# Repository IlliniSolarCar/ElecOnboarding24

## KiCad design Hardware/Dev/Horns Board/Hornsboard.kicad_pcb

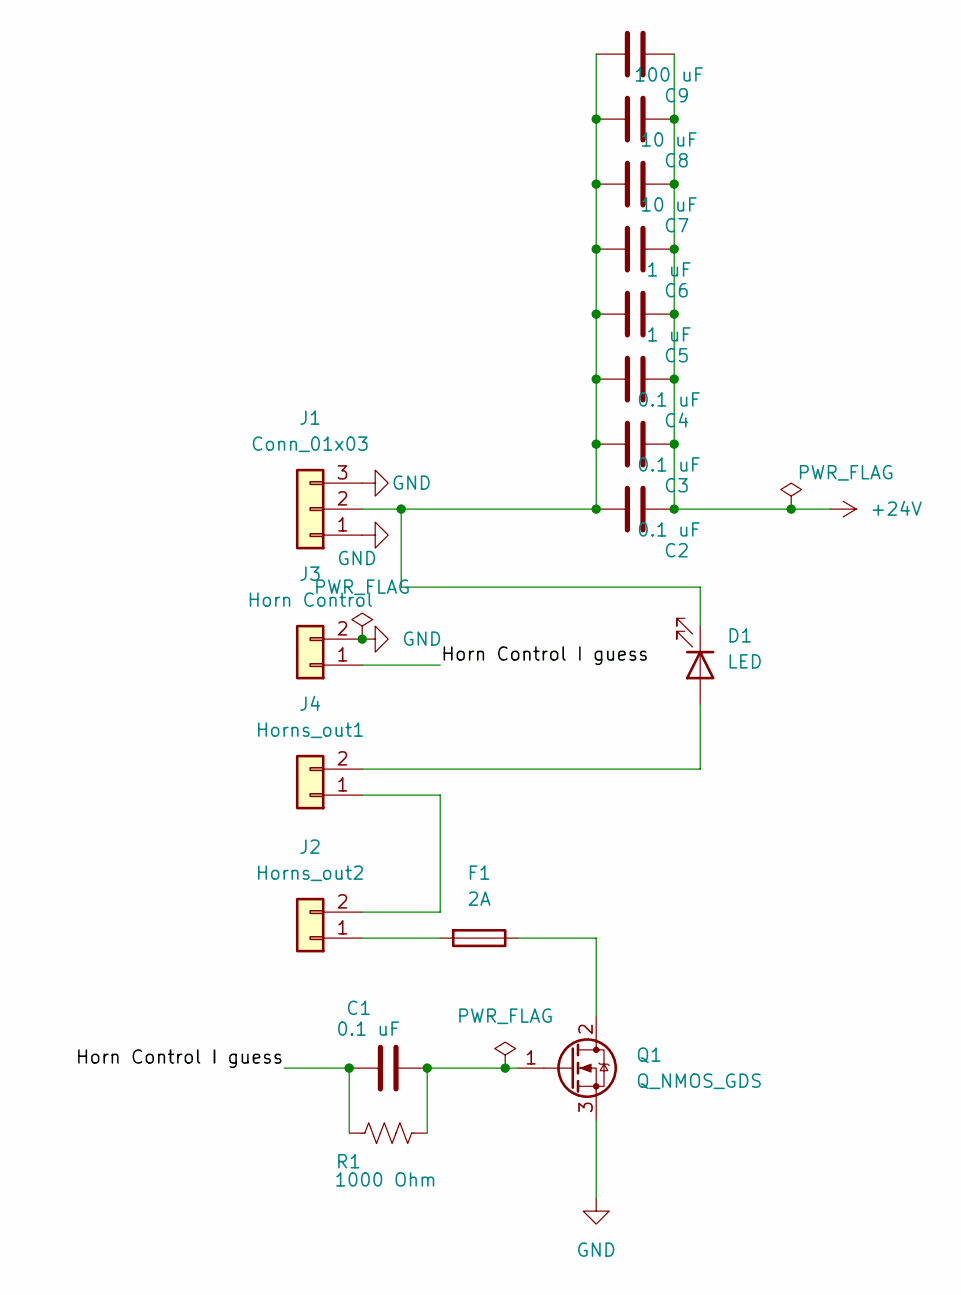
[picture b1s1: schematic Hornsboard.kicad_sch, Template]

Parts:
C1, C2, C3, C4: 0.1 uF; C_0603_1608Metric_Pad1.08x0.95mm_HandSolder
C5, C6: 1 uF; C_0603_1608Metric_Pad1.08x0.95mm_HandSolder
C7, C8: 10 uF; C_0603_1608Metric_Pad1.08x0.95mm_HandSolder
C9: 100 uF; C_0603_1608Metric_Pad1.08x0.95mm_HandSolder
D1: LED; LED_0603_1608Metric_Pad1.05x0.95mm_HandSolder
F1: 2A; Fuse_0603_1608Metric
J1: Conn_01x03; Molex_Micro-Fit_3.0_43650-0300_1x03_P3.00mm_Horizontal
J2: Horns_out2; Molex_Micro-Fit_3.0_43650-0200_1x02_P3.00mm_Horizontal
J3: Horn Control; Molex_Micro-Fit_3.0_43650-0200_1x02_P3.00mm_Horizontal
J4: Horns_out1; Molex_Micro-Fit_3.0_43650-0200_1x02_P3.00mm_Horizontal
Q1: Q_NMOS_GDS; TO-252-2
R1: 1000 Ohm; R_0603_1608Metric_Pad0.98x0.95mm_HandSolder

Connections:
+24V: C2.2, C3.2, C4.2, C5.2, C6.2, C7.2, C8.2, C9.2
/Horn Control I guess: C1.1, J3.1, R1.1
GND: J1.1, J1.3, J3.2, Q1.3 (S)
unnamed: D1.2 (A), J4.2
unnamed: C2.1, C3.1, C4.1, C5.1, C6.1, C7.1, C8.1, C9.1, D1.1 (K), J1.2
unnamed: F1.2, J2.1
unnamed: J2.2, J4.1
unnamed: F1.1, Q1.2 (D)
unnamed: C1.2, Q1.1 (G), R1.2

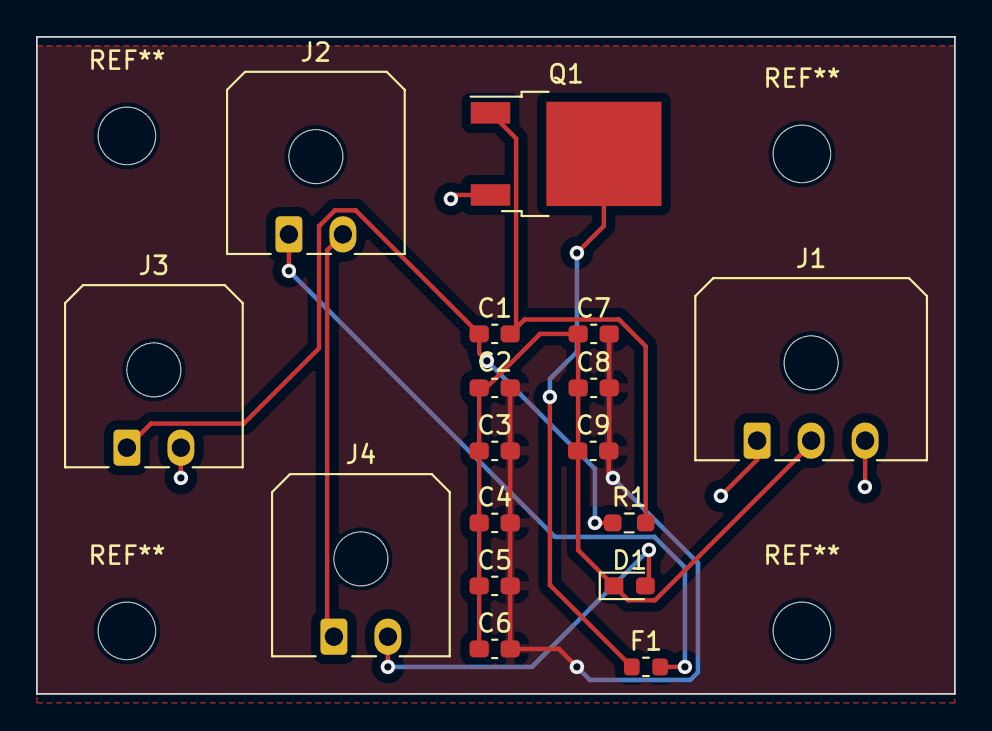
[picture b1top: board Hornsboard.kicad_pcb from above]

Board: 2 copper layers, 51.0 x 36.5 mm, 17 parts (0 on the bottom side), 9 nets.

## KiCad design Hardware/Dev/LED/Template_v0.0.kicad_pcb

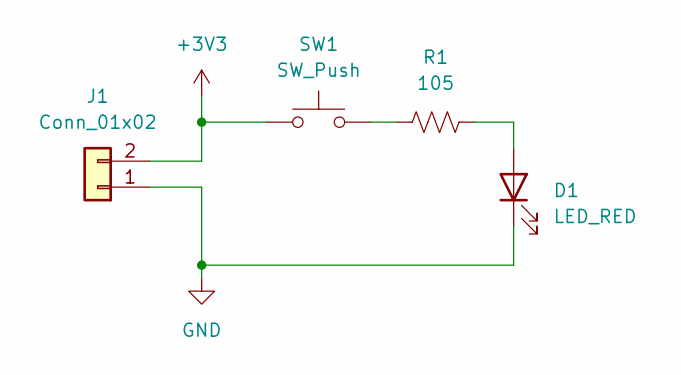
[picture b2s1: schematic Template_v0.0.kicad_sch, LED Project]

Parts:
D1: LED_RED; LED_0603_Symbol_on_F.SilkS
J1: Conn_01x02; Molex_KK-254_AE-6410-02A_1x02_P2.54mm_Vertical; MPN 022272021
R1: 105; R_0603_1608Metric_Pad0.98x0.95mm_HandSolder
SW1: SW_Push; SW_DIP_SPSTx01_Slide_6.7x4.1mm_W8.61mm_P2.54mm_LowProfile; MPN 1825910-6

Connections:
+3V3: J1.2, SW1.1
GND: D1.1 (K), J1.1
unnamed: D1.2 (A), R1.2
unnamed: R1.1, SW1.2

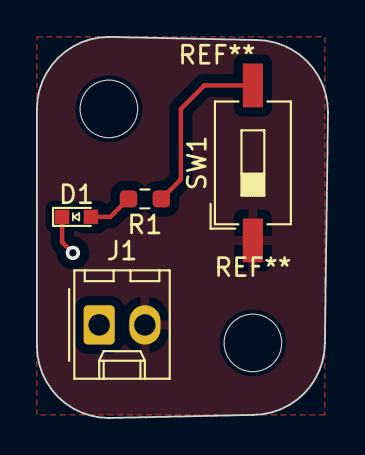
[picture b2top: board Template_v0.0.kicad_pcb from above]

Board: 2 copper layers, 16.2 x 21.2 mm, 4 parts (0 on the bottom side), 4 nets.

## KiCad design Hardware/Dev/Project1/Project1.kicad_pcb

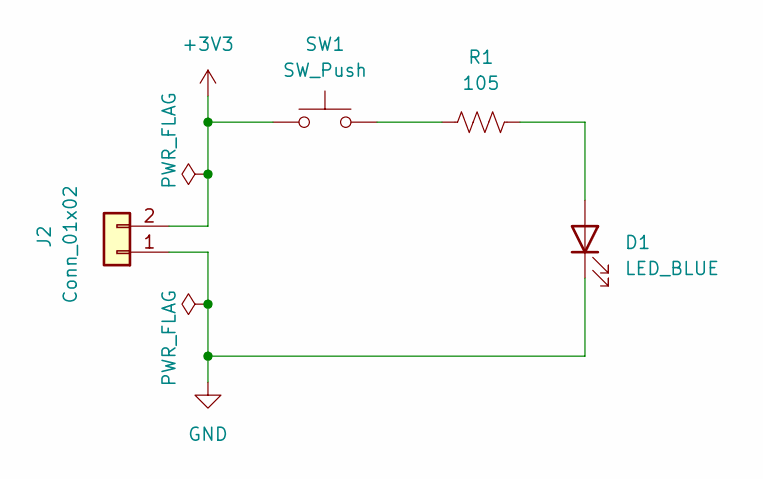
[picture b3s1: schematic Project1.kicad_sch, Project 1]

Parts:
D1: LED_BLUE; LED_0603_Symbol_on_F.SilkS
J2: Conn_01x02; Molex_KK-254_AE-6410-02A_1x02_P2.54mm_Vertical; MPN 022272021
R1: 105; R_0603_1608Metric_Pad0.98x0.95mm_HandSolder
SW1: SW_Push; SW_DIP_SPSTx01_Slide_6.7x4.1mm_W8.61mm_P2.54mm_LowProfile; MPN 1825910-6

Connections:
+3V3: J2.2, SW1.1
GND: D1.1 (K), J2.1
unnamed: D1.2 (A), R1.1
unnamed: R1.2, SW1.2

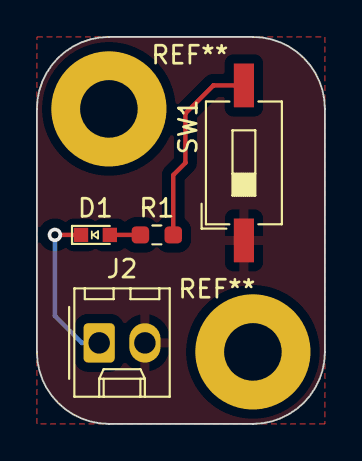
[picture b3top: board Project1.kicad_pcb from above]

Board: 2 copper layers, 16.0 x 21.5 mm, 4 parts (0 on the bottom side), 4 nets.
